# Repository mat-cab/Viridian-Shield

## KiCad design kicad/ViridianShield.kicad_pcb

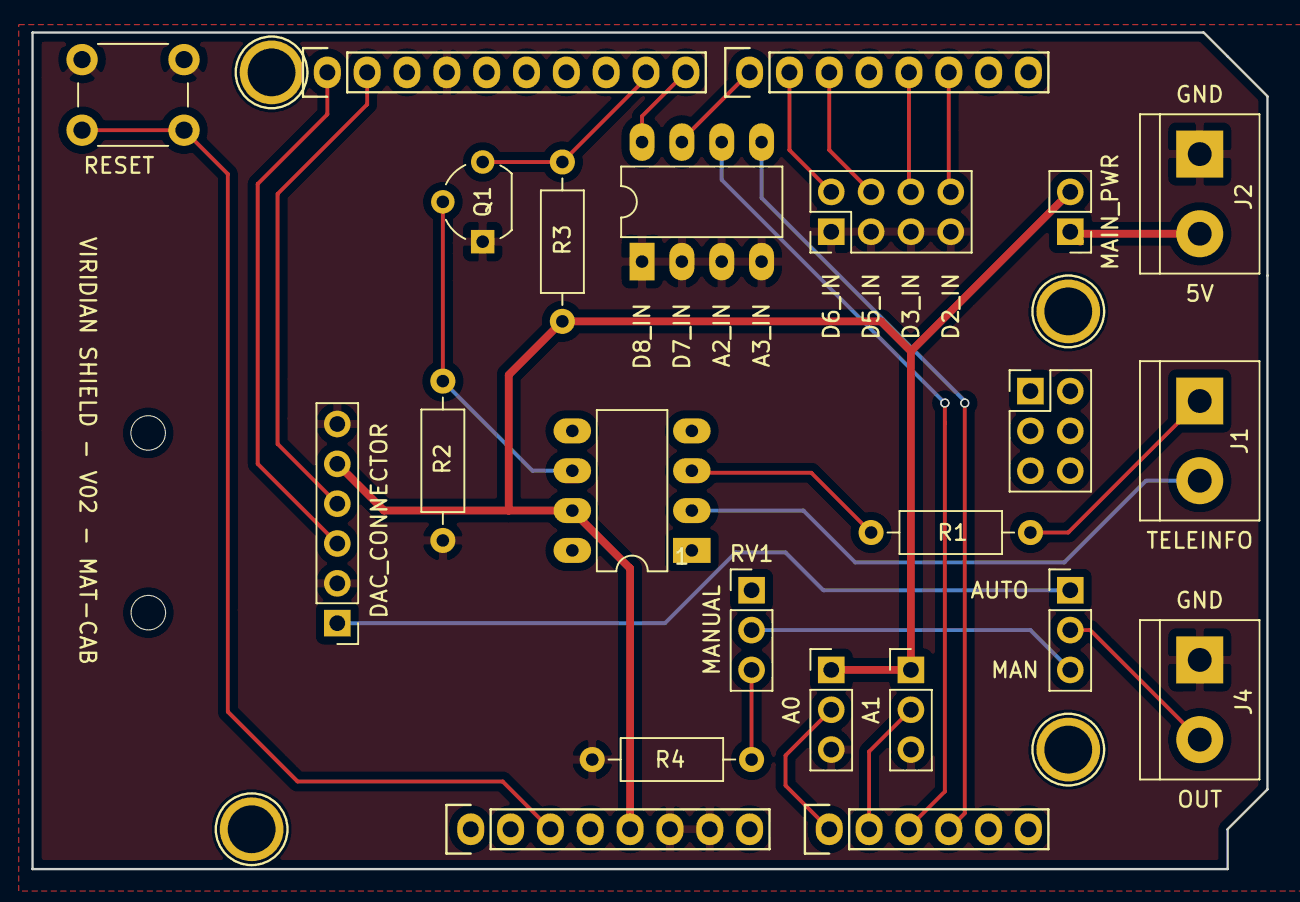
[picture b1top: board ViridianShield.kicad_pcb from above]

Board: 2 copper layers, 78.7 x 53.3 mm, 27 parts (0 on the bottom side), 25 nets.

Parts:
J1: TELEINFO_INPUT; TerminalBlock_bornier-2_P5.08mm
J2: POWER_INPUT; TerminalBlock_bornier-2_P5.08mm
J3: DAC_MODULE; PinHeader_1x06_P2.54mm_Vertical
J4: VIRIDIAN_CONNECTOR; TerminalBlock_bornier-2_P5.08mm
P1: Power; Socket_Strip_Arduino_1x08
P2: Analog; Socket_Strip_Arduino_1x06
P3: Digital; Socket_Strip_Arduino_1x10
P4: Digital; Socket_Strip_Arduino_1x08
P5, P6, P7, P8: CONN_01X01; Arduino_1pin
P9: Conn_02x03_Odd_Even; PinHeader_2x03_P2.54mm_Vertical
Q1: 2N7000; TO-92_Wide
R1: 1.6k; R_Axial_DIN0207_L6.3mm_D2.5mm_P10.16mm_Horizontal
R2, R3: 10k; R_Axial_DIN0207_L6.3mm_D2.5mm_P10.16mm_Horizontal
R4: 240; R_Axial_DIN0207_L6.3mm_D2.5mm_P10.16mm_Horizontal
RV1: MANUAL_INPUT; PinHeader_1x03_P2.54mm_Vertical
RV2: A0_INPUT; PinHeader_1x03_P2.54mm_Vertical
RV3: A1_INPUT; PinHeader_1x03_P2.54mm_Vertical
SW1: INTERNAL_SWITCHES; DIP-8_W7.62mm_LongPads
SW2: D2-6_INPUT_SWITCHES; PinHeader_2x04_P2.54mm_Vertical_OtherPinAlloc
SW3: MAIN_POWER_SWITCH; PinHeader_1x02_P2.54mm_Vertical
SW4: AUTO_MANUAL_SWITCH; PinHeader_1x03_P2.54mm_Vertical
SW5: RESET_SWITCH; SW_PUSH_6mm
U1: SFH620A-1; DIP-8-4_W7.62mm_LongPads

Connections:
+5V: J3.5, P1.5, R3.1, RV2.1, RV3.1, SW3.2, U1.4
/A0: P2.1, RV2.2
/A1: P2.2, RV3.2
/A2: P2.3, SW1.6
/A3: P2.4, SW1.5
/D2: P4.6, SW2.5
/D3: P4.5, SW2.6
/D5: P4.3, SW2.7
/D6: P4.2, SW2.8
/D7: P4.1, SW1.7
/D8: P3.10, SW1.8
/D9: P3.9, Q1.3, R3.2
/MANUAL_OUTPUT: RV1.2, SW4.3
/RESET: P1.3, SW5.2
/SCL: J3.3, P3.1
/SDA: J3.4, P3.2
GND: J2.1, J3.2, J3.6, J4.1, P1.6, P1.7, P3.4, Q1.1, R2.2, R4.2, RV2.3, RV3.3, SW1.1, SW1.2, SW1.3, SW1.4, SW2.1, SW2.2, SW2.3, SW2.4, SW5.1
unnamed: J1.1, R1.2
unnamed: J1.2, U1.1
unnamed: J2.2, SW3.1
unnamed: J3.1, SW4.1
unnamed: J4.2, SW4.2
unnamed: Q1.2, R2.1, U1.3
unnamed: R1.1, U1.2
unnamed: R4.1, RV1.3

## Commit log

2020-12-15 kicad: Added version 01 of schematics
2020-12-15 Initial version of debug
    Only available for MEGA
2020-12-15 Added MEGA env to platformIO
2020-12-15 inputs: changed precompiler macro to static const definitions
2020-12-15 debug: Possibility to force output for Uno
2020-12-15 inputs: Added function to read the variable (analog) inputs
2020-12-15 debug: updated for Mega platform
2020-12-15 debug: correction of serial start
2020-12-15 inputs: minor cosmetic changes
2020-12-15 inputs: realigned options/variables with project
2020-12-15 debug: using statc functions only
    This will be easier than OOP
2020-12-15 dac_MCP4725: Initial version for dac communication
2020-12-15 Debug: Moved variable definitions to header file
2020-12-15 Inputs: Initial version for digital inputs
2020-12-15 inputs: correction in read function
    digitalRead does not return bool but LOW/HIGH
2020-12-15 dac_MCP4725: Improved debug level
2020-12-15 viridian: now new current applies immediately
    Also changed the debug messages with the module name
2020-12-15 debug: Correction for MEGA
    Should use Serial3, otherwise SDA (I2C) pin is also used
2020-12-15 timer: creation of class to handle long cycles
2020-12-15 viridian: created viridian class
2020-12-15 viridian: add message log in case of undercharging
2020-12-15 teleInfo: Added submodule
2020-12-15 main: creation of intial version
2020-12-15 main: added log of teleinfo data
2020-12-15 main: Changed logic in case of ADPS
2020-12-15 main: corrected ADPS behavior
    After second reading, ADPS is not stored
2020-12-15 main: addition of a delay at the end of setup
    This allows the home power grid to fuly come back up
2020-12-15 main: added condition to start charge
2020-12-15 main: minor debug message update
2020-12-15 main: moved teleinfo log to debug
2020-12-15 main: added definition for loop duration
2020-12-15 viridian: renamed private variables with prefix
2020-12-15 teleinfo: added/corrected expected labels
2020-12-15 teleinfo: improved robustness with end of lines
2020-12-15 teleinfo: removed external library and created own
    External library is using SoftwareSerial
    which is not compatible with real HardwareSerial
2020-12-15 teleinfo: added debug messages
2020-12-15 teleinfo: corrected string equality checks
2020-12-15 main: added teleinfo check after viridian command
2020-12-15 teleinfo: Increased value buffer size
    Apparently for ADCO, 12 is not enough
2020-12-15 main: added debug message for offline charger
2020-12-15 teleinfo: corrected overflow detection
2020-12-15 inputs: add 1A margin option on D9
2020-12-15 teleinfo: added debug message for labels and value
2020-12-15 main: no current change for less than 1 amp
2020-12-15 viridian: Added check of current change
2020-12-15 viridian: correction for currentChanged definition
2020-12-15 teleinfo: added static definition for const vars
2020-12-15 viridian: corrected Q computation
    Math was wrong!
2020-12-15 main: added debug message before charge change
2020-12-27 main: added charging car input
    When the car is not charging, set a nominal charge to 10A
2020-12-27 viridian: added measured offset
    For some reason, the viridian allows more than the command
2020-12-27 main: 2A margin option changed to ISOUSC multiply
2020-12-27 main: cosmetic - updated indentation
2020-12-27 debug: removed FORCE_DEBUG for UNO
    This option is probably not working, because Serial is used for Teleinfo
2021-02-26 main: added initial charge delay
    This allows the general power consumption to settle before adjusting
2021-02-26 main: Correction of wrong logic for car charging
2021-02-26 main: Added delay after charge adaptation
2021-02-26 main: Corrected control for minimum current change
2021-02-26 main: Lowered adjusting frequency to 15 mins
2021-02-26 teleinfo: Added defaut values
2021-02-26 viridian: force initial command at 0
2021-05-29 kicad: Shield design evolution
2021-05-29 debug: stored messages in FLASH memory
    This allows to free about 40% of the RAM for UNO
2021-05-29 teleinfo: fixed warning message in initialization
2021-05-29 teleinfo: changed HardwareSerial to SoftwareSerial
    This is better given that serial speeds are very slow
    it also allows to use HardwareSerial to perform debugging on Arduino Uno
2021-05-29 debug: Always use Serial for debugging
    On Uno and on Mega
2021-05-29 platformio: removed mega upload/monitor particularities
2021-05-29 gitignore: Updated to exclude kicad files
2021-05-29 kicad: V02 Shield update
2021-05-29 platformio: Removed compatibility with MEGA
    Now UNO should be enough, given that it is possible to debug with it
2021-07-11 inputs: Updated adressing for V02 shield
2021-07-11 teleinfo: Updated addressing for V02 shield
2021-07-11 inputs: Corrected initialization for uno and V02 shield
2021-07-11 main: added debug message in setup
    Now we have a clearer view of when the setup is really finished
2021-07-11 main: minor cosmetic corrections
2021-07-11 teleinfo: Implemented timeout mecanism on read
    Allows for better debugging, hopefully.
    However for production, timeout shall be very big, so that nothing is performed without appropriate info
